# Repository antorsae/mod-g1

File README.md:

# mod-g1

Pendiente:

- [ ] Cambiar R1 por otra más grande.
- [ ] Marcar GND en los conectores.
- [ ] Subir algo de ayuda a la instalación.
- [ ] Incluir circuiteria de G1 máximo durante el retrazo horizontal (o blacking).

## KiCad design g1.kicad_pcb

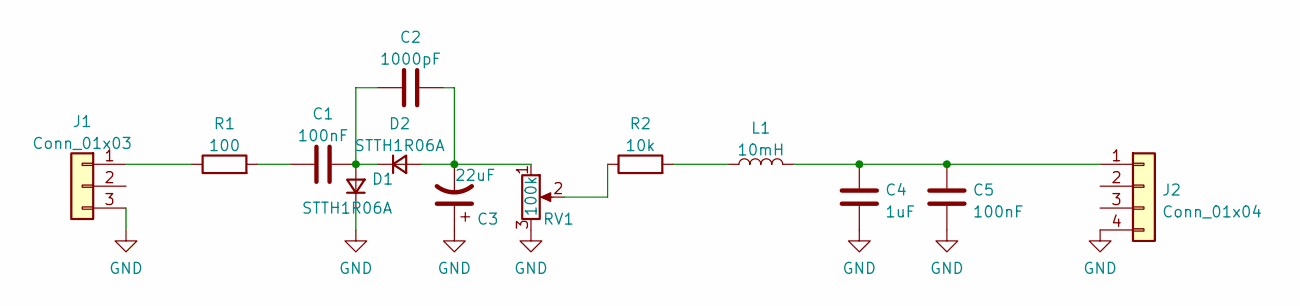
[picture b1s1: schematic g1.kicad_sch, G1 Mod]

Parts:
C1, C5: 100nF; C_1210_3225Metric; MPN C342668
C2: 1000pF; C_1206_3216Metric; MPN C35216
C3: 22uF; CP_Elec_16x17.5; MPN C249612
C4: 1uF; C_1812_4532Metric; MPN C381468
D1, D2: STTH1R06A; D_SMA; MPN C13337
J1: Conn_01x03; JST_XH_B3B-XH-A_1x03_P2.50mm_Vertical; MPN C144394
J2: Conn_01x04; JST_XH_B4B-XH-A_1x04_P2.50mm_Vertical; MPN C144395
L1: 10mH; L_12x12mm_H6mm; MPN C718296
R1: 100; R_1206_3216Metric; MPN C17901
R2: 10k; R_1206_3216Metric; MPN C17902
RV1: 100k; TRIM_3313J-1-103E; MPN C89235

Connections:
GND: C3.1, C4.1, C5.1, D1.1 (K), J1.3, J2.4, RV1.3
unnamed: C1.1, R1.2
unnamed: C1.2, C2.1, D1.2 (A), D2.1 (K)
unnamed: C2.2, C3.2, D2.2 (A), RV1.1
unnamed: C4.2, C5.2, J2.1, L1.2
unnamed: J1.1, R1.1
unnamed: L1.1, R2.2
unnamed: R2.1, RV1.2

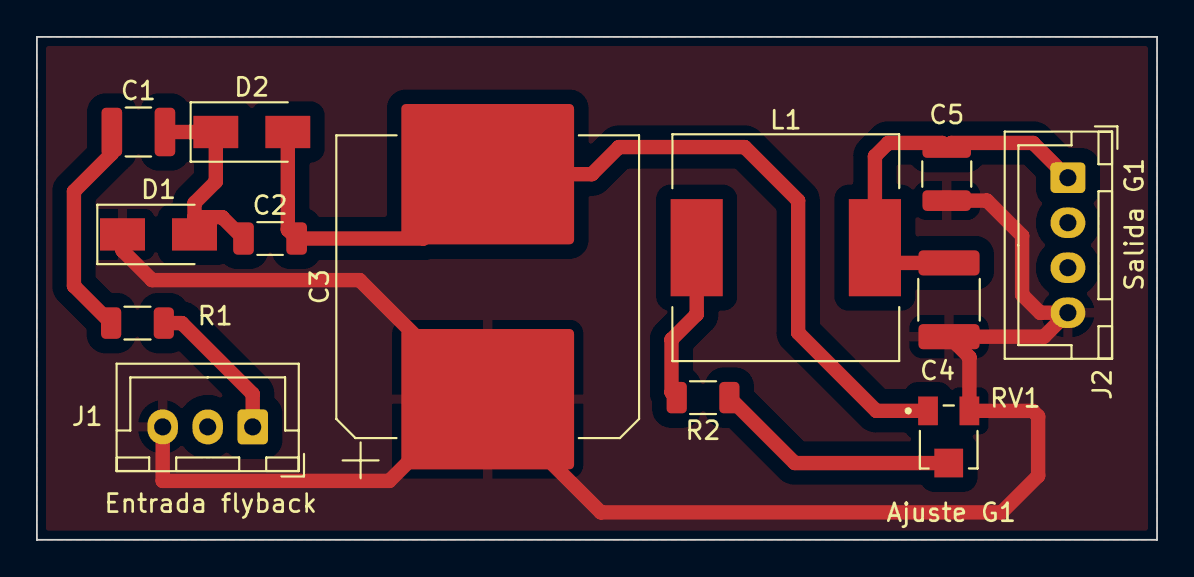
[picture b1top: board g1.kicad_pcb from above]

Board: 2 copper layers, 62.2 x 27.9 mm, 13 parts (0 on the bottom side), 8 nets.

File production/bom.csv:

Designator,Footprint,Quantity,Value,LCSC Part #
"C1, C5",C_1210_3225Metric,2,100nF,C342668
C2,C_1206_3216Metric,1,1000pF,C35216
C3,CP_Elec_16x17.5,1,22uF,C249612
C4,C_1812_4532Metric,1,1uF,C381468
"D1, D2",D_SMA,2,STTH1R06A,C13337
J1,JST_XH_B3B-XH-A_1x03_P2.50mm_Vertical,1,Conn_01x03,C144394
J2,JST_XH_B4B-XH-A_1x04_P2.50mm_Vertical,1,Conn_01x04,C144395
L1,L_12x12mm_H6mm,1,10mH,C718296
R1,R_1206_3216Metric,1,100,C17901
R2,R_1206_3216Metric,1,10k,C17902
RV1,TRIM_3313J-1-103E,1,100k,C89235

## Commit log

2023-04-29 1st sub
